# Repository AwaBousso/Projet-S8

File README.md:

# Projet-S8 Voiture Autonome

ESIGELEC 2018

Amaury Reille

Léo Abalan

Awa Bousso

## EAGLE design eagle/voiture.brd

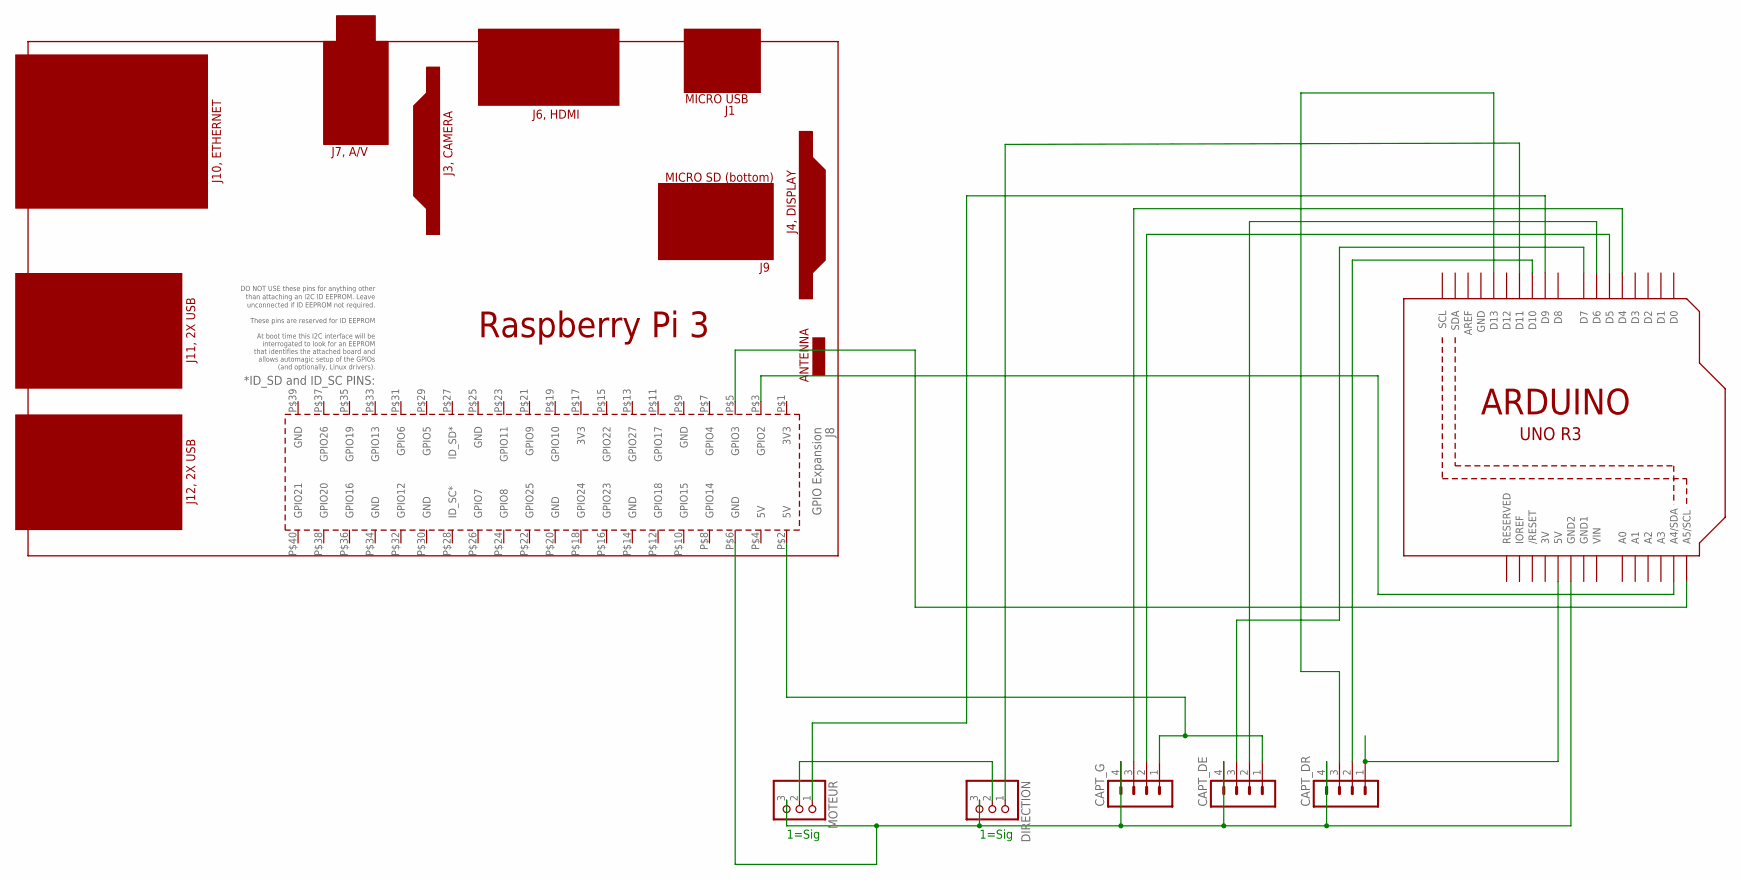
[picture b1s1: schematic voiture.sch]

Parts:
CAPT_DE: MA04-1
CAPT_DR: MA04-1
CAPT_G: MA04-1
DIRECTION: PINHD-1X3; 1X03
MOTEUR: PINHD-1X3; 1X03
PCB1: RPI3
U1: ARDUINOR3-BPLACE

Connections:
3V: U1.3V
GND: U1.GND
GND1: U1.GND1
unnamed: DIRECTION.2, MOTEUR.2
unnamed: CAPT_DE.4, CAPT_DR.4, CAPT_G.4, DIRECTION.3, MOTEUR.3, PCB1.P$6 (GND), U1.GND2
unnamed: DIRECTION.1, U1.D11
unnamed: MOTEUR.1, U1.D9
unnamed: CAPT_DR.1, U1.5V
unnamed: CAPT_DE.3, U1.D7
unnamed: CAPT_DE.2, U1.D6
unnamed: PCB1.P$3 (GPIO2), U1.A4 (A4/SDA)
unnamed: PCB1.P$5 (GPIO3), U1.A5 (A5/SCL)
unnamed: CAPT_G.2, U1.D5
unnamed: CAPT_G.3, U1.D4
unnamed: CAPT_DR.2, U1.D10
unnamed: CAPT_DR.3, U1.D13
unnamed: CAPT_DE.1, CAPT_G.1, PCB1.P$2 (5V)
VIN: U1.VIN

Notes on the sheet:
1=Sig

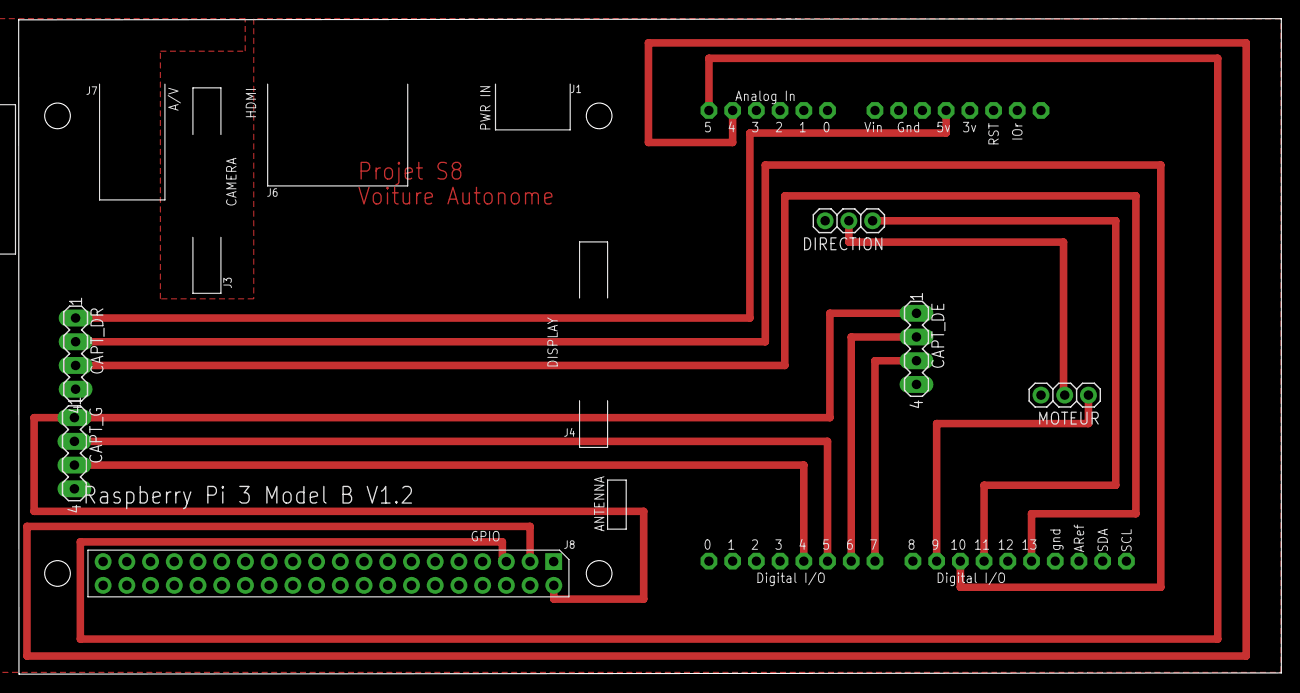
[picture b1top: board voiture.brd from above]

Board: 2 copper layers, 135.2 x 70.2 mm, 7 parts (0 on the bottom side), 14 nets.

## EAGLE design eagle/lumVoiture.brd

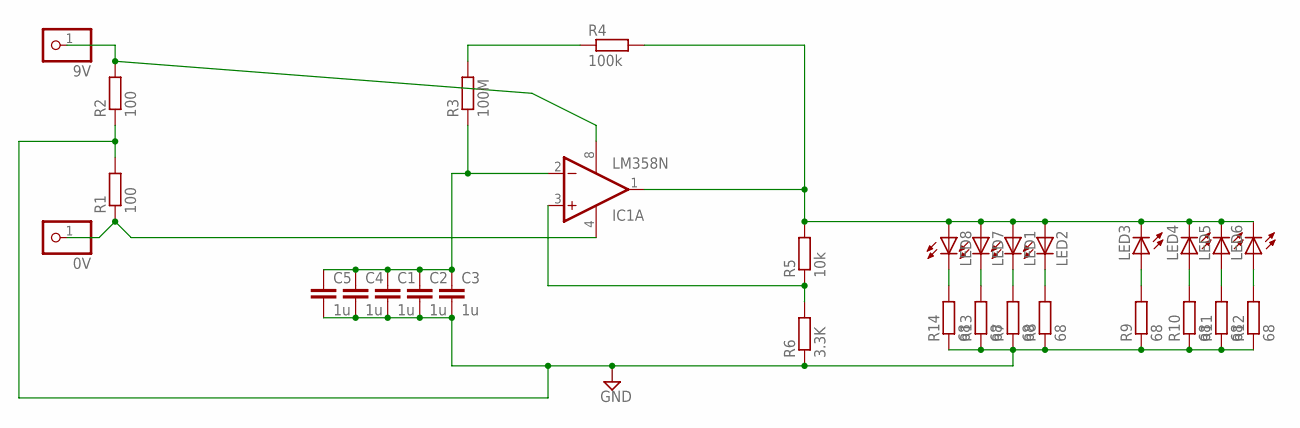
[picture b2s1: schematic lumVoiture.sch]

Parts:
0V, 9V: PINHD-1X1; 1X01
C1, C2, C3, C4, C5: 1u; C025-025X050
IC1: LM358N; DIL08
LED1, LED2, LED3, LED4, LED5, LED6, LED7, LED8: LED5MM
R1, R2: 100; 0207/10
R3: 100M; 0207/10
R4: 100k; 0207/10
R5: 10k; 0207/10
R6: 3.3K; 0207/10
R7, R8, R9, R10, R11, R12, R13, R14: 68; 0207/10

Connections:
GND: C1.2, C2.2, C3.2, C4.2, C5.2, R1.2, R2.1, R6.1, R7.1, R8.1, R9.1, R10.1, R11.1, R12.1, R13.1, R14.1
unnamed: LED1.K (C), R7.2
unnamed: R3.2, R4.1
unnamed: 0V.1, IC1.4 (V-), R1.1
unnamed: IC1.3 (+IN), R5.1, R6.2
unnamed: LED2.K (C), R8.2
unnamed: C1.1, C2.1, C3.1, C4.1, C5.1, IC1.2 (-IN), R3.1
unnamed: LED3.A, R9.2
unnamed: LED4.A, R10.2
unnamed: LED8.K (C), R14.2
unnamed: IC1.1 (OUT), LED1.A, LED2.A, LED3.K (C), LED4.K (C), LED5.K (C), LED6.K (C), LED7.A, LED8.A, R4.2, R5.2
unnamed: LED7.K (C), R13.2
unnamed: 9V.1, IC1.8 (V+), R2.2
unnamed: LED5.A, R11.2
unnamed: LED6.A, R12.2

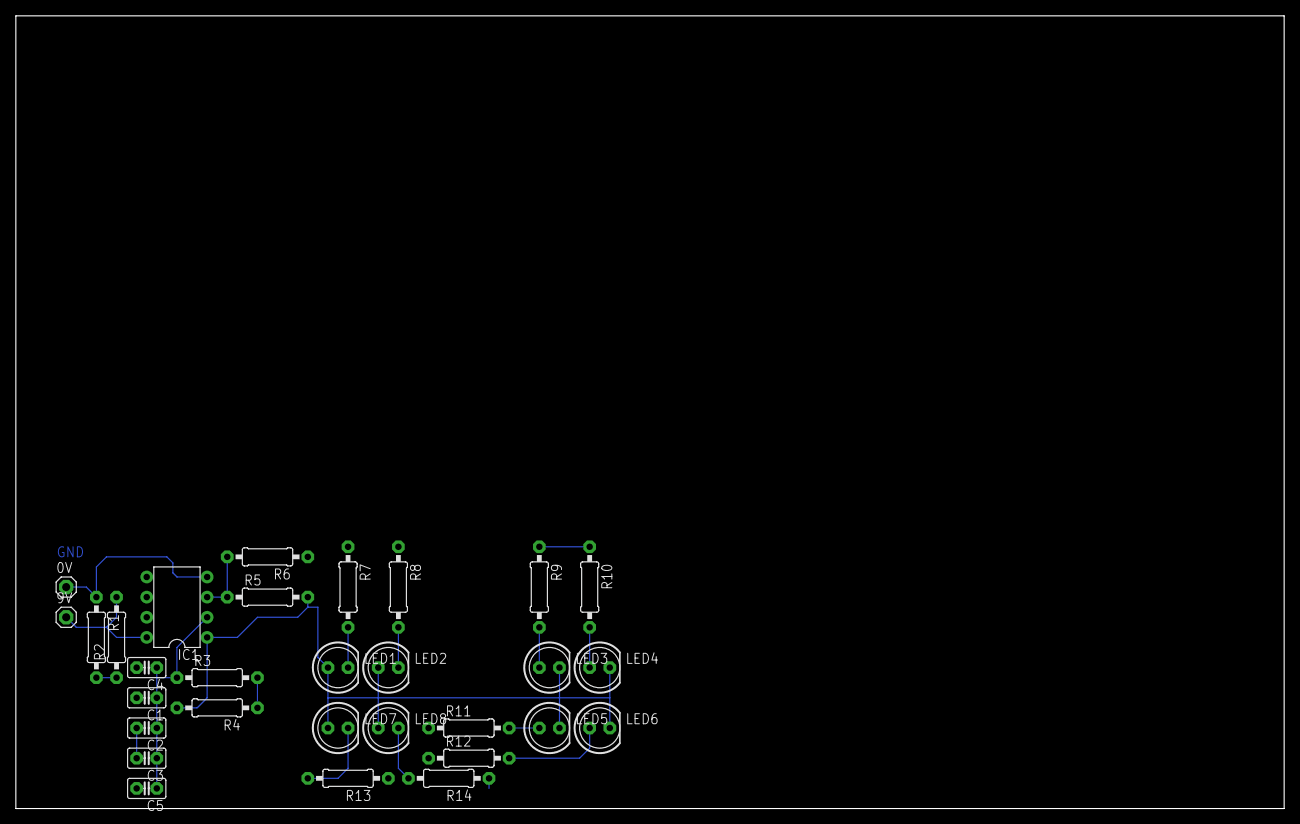
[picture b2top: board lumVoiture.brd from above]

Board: 2 copper layers, 160.0 x 100.0 mm, 30 parts (0 on the bottom side), 15 nets.

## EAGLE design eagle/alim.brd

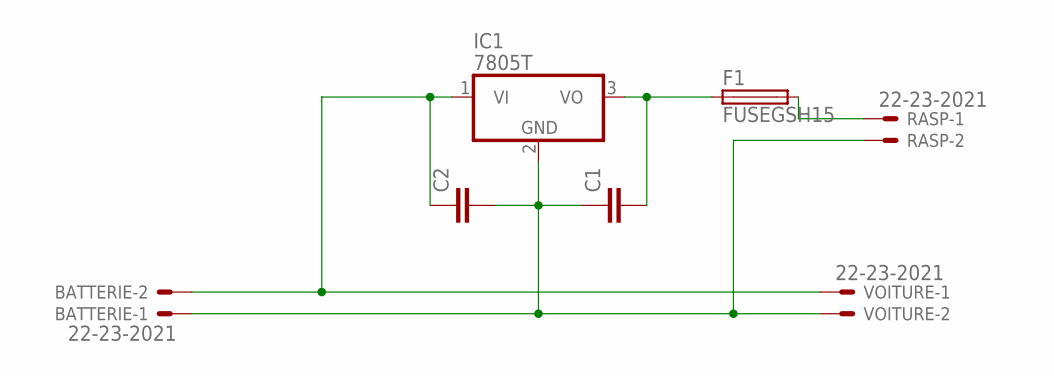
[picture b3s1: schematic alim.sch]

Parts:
BATTERIE: 22-23-2021
C1, C2: C-EU025-025X050; C025-025X050
F1: FUSEGSH15; GSH15
IC1: 7805T; TO220H
RASP: 22-23-2021
VOITURE: 22-23-2021

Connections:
unnamed: BATTERIE.2, C2.1, IC1.1 (VI), VOITURE.1
unnamed: BATTERIE.1, C1.1, C2.2, IC1.2 (GND), RASP.2, VOITURE.2
unnamed: C1.2, F1.1, IC1.3 (VO)
unnamed: F1.2, RASP.1

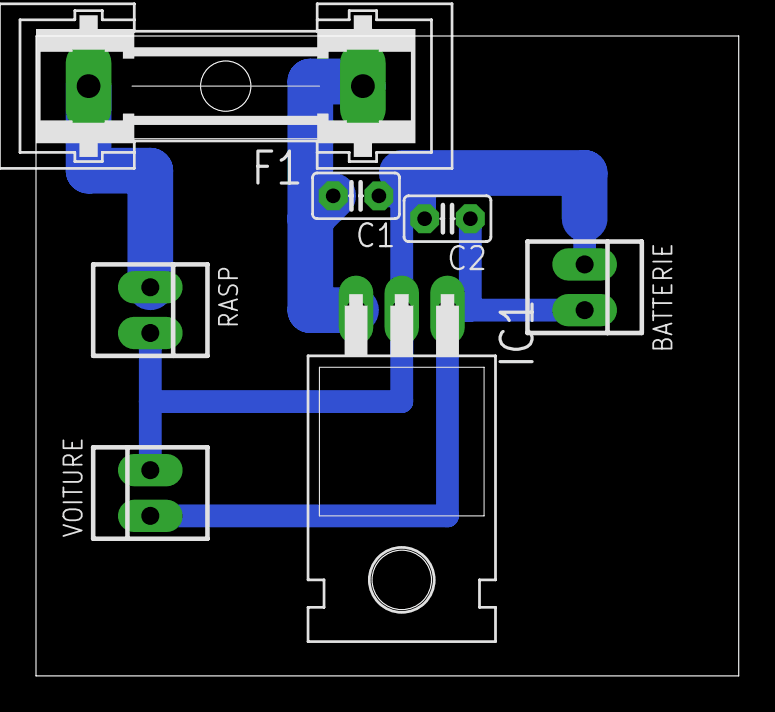
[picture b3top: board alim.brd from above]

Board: 2 copper layers, 39.0 x 35.5 mm, 7 parts (0 on the bottom side), 4 nets.

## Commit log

2018-04-23 Update README.md
    @amaury-esig
